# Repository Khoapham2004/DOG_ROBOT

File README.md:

# DOG_ROBOT
First, this project focuses on the research and development of a quadruped robot (Dog Robot). Our team used the mechanical design of the open-source DINGO Quadruped Robot as a reference. The electronic hardware, PCB design, overall kinematics, control algorithms, and software source code were entirely designed and implemented by our team.

This GitHub repository includes the complete project source code, including the Raspberry Pi software, image processing module, robot control commands, firmware for the custom PCB, the software developed to operate the robot, and the complete electrical schematic of the system.

GENERAL

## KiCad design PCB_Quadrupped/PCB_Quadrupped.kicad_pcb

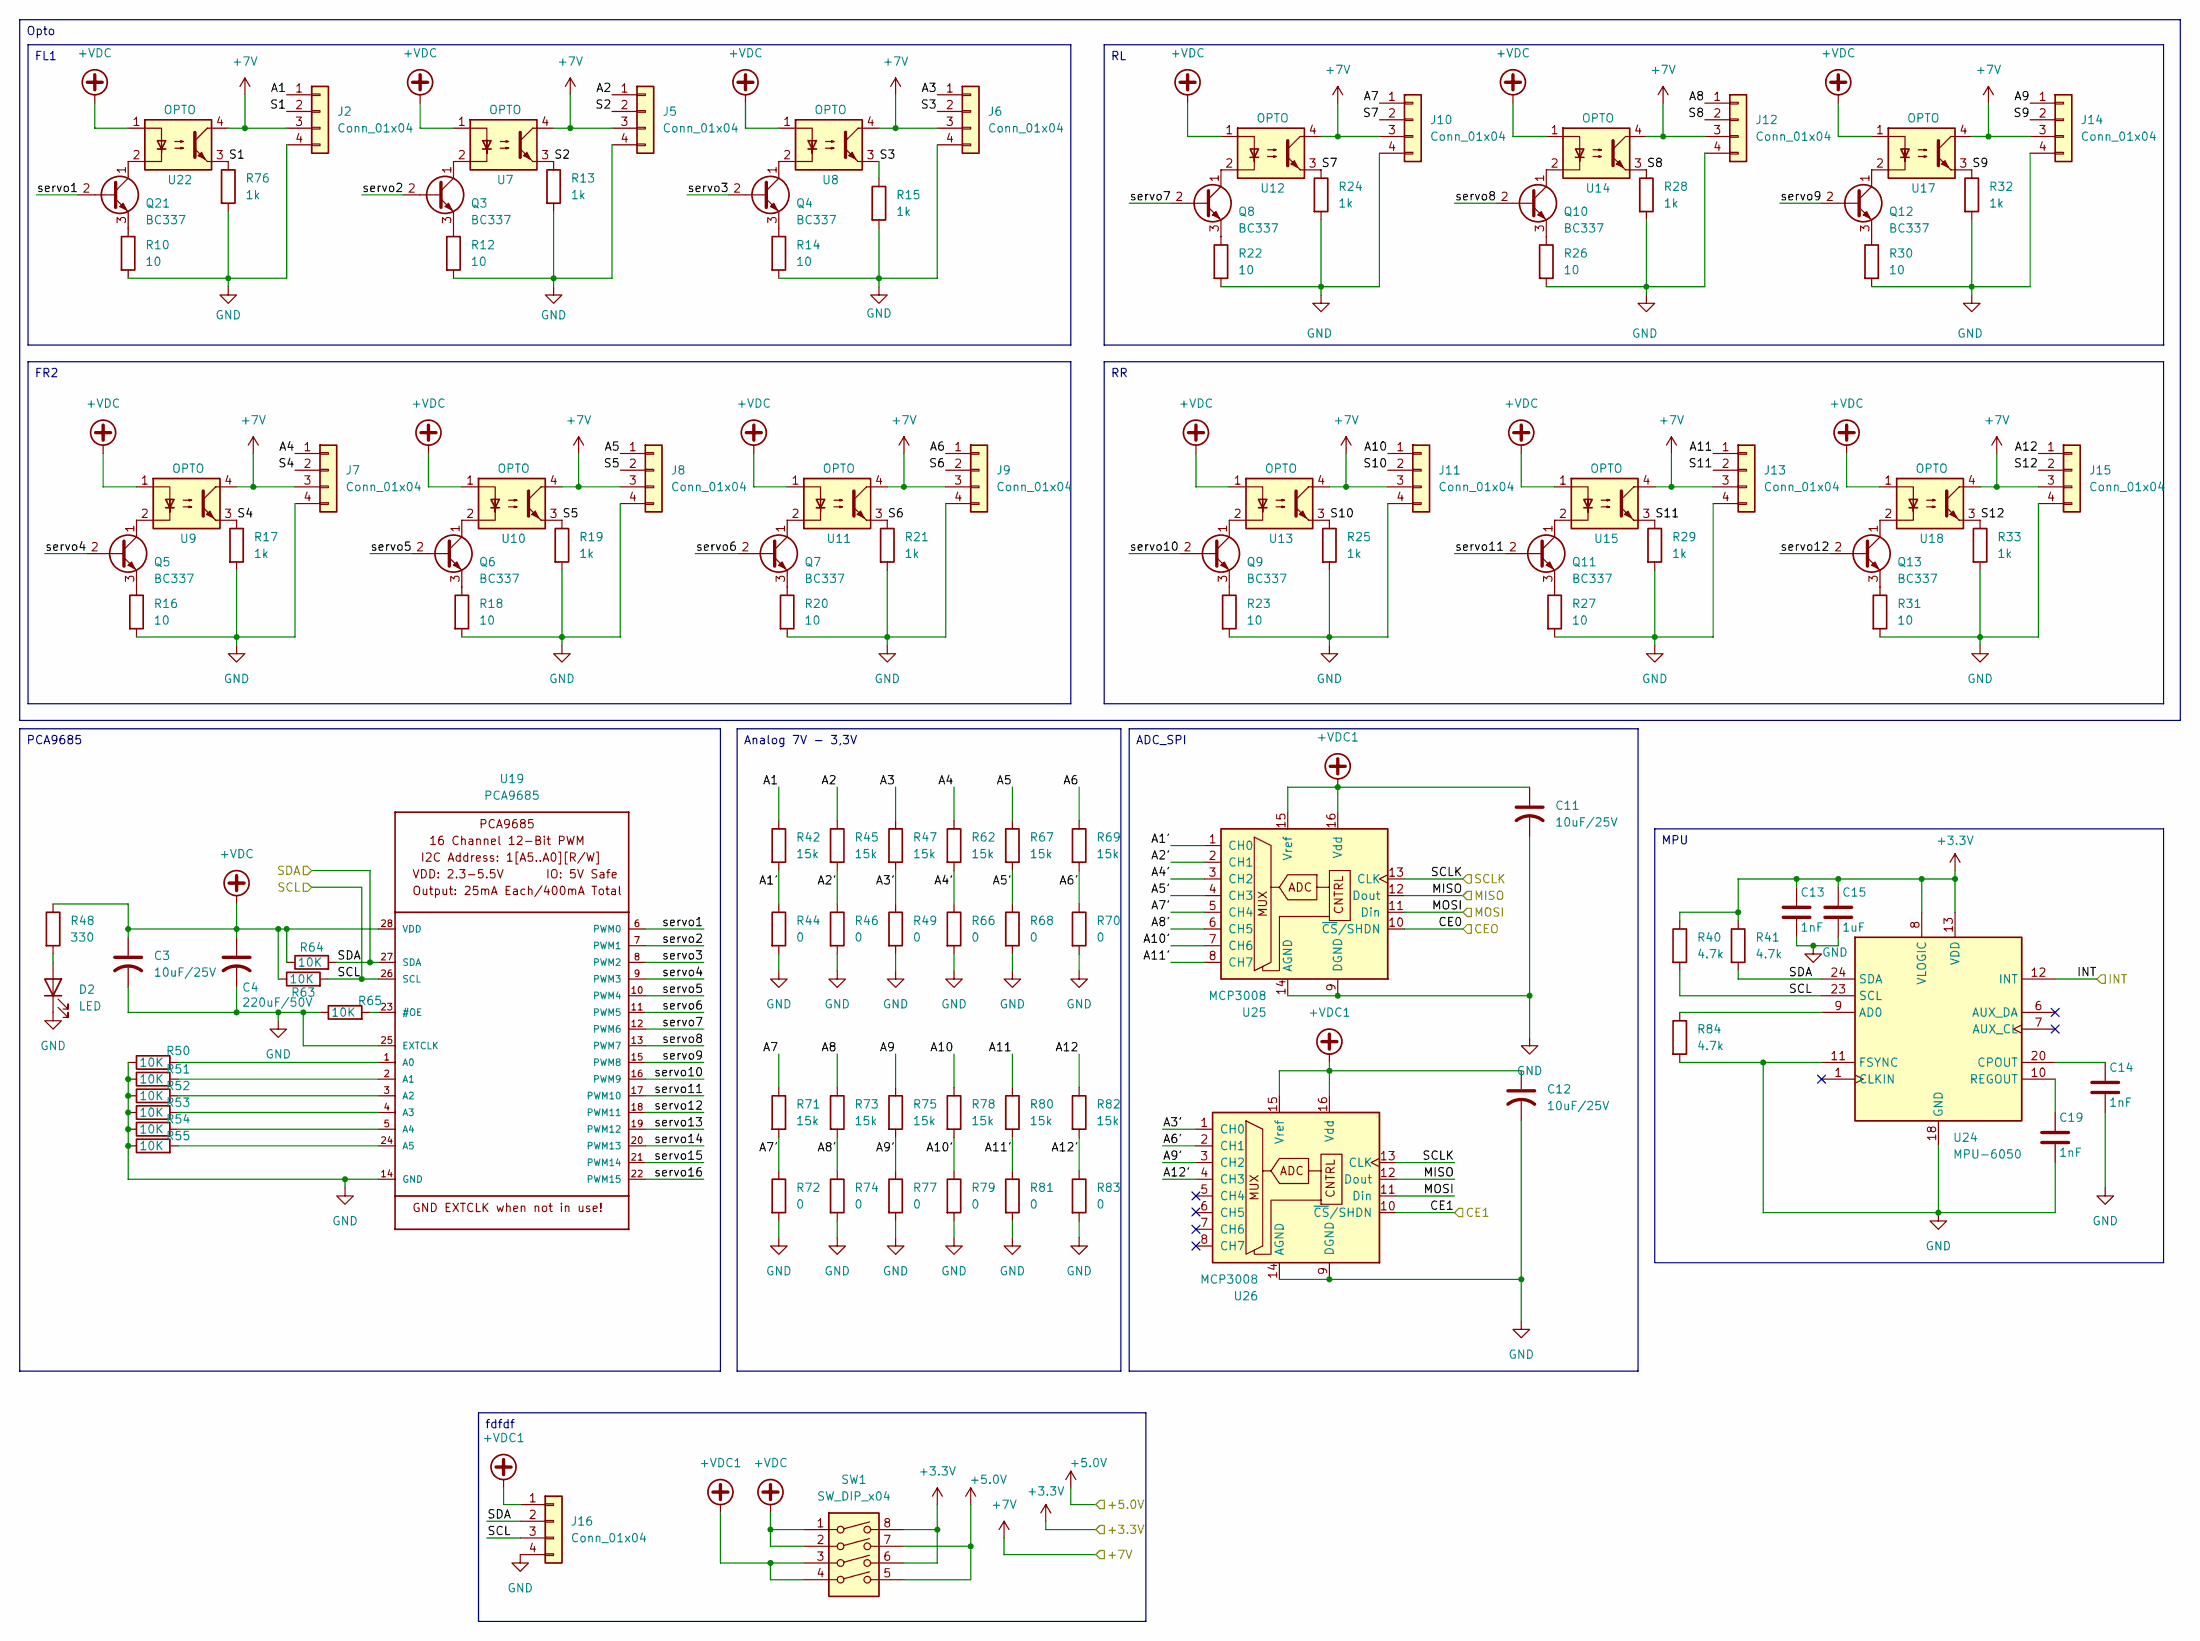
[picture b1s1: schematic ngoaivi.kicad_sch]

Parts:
C3, C11, C12: 10uF/25V; CP_Elec_4x4.5
C4: 220uF/50V; CP_Elec_10x10.5
C13, C14, C19: 1nF; C_0805_2012Metric
C15: 1uF; C_0805_2012Metric
D2: LED; LED_0805_2012Metric
J2, J5, J6, J7, J8, J9, J10, J11, J12, J13, J14, J15: Conn_01x04; JST_B4B-XH-A_LF__SN_
J16: Conn_01x04; PinHeader_1x04_P2.54mm_Vertical_SMD_Pin1Right
Q3, Q4, Q5, Q6, Q7, Q8, Q9, Q10, Q11, Q12, Q13, Q21: BC337; TO-92_Inline
R10, R12, R14, R16, R18, R20, R22, R23, R26, R27, R30, R31: 10; R_0805_2012Metric_Pad1.20x1.40mm_HandSolder
R13, R15, R17, R19, R21, R24, R25, R28, R29, R32, R33, R76: 1k; R_0805_2012Metric_Pad1.20x1.40mm_HandSolder
R40, R41, R84: 4.7k; R_0805_2012Metric_Pad1.20x1.40mm_HandSolder
R42, R45, R47, R62, R67, R69, R71, R73, R75, R78, R80, R82: 15k; R_0805_2012Metric_Pad1.20x1.40mm_HandSolder
R44, R46, R49, R66, R68, R70, R72, R74, R77, R79, R81, R83: 0; R_0805_2012Metric_Pad1.20x1.40mm_HandSolder
R48: 330; R_0805_2012Metric_Pad1.20x1.40mm_HandSolder
R50, R51, R52, R53, R54, R55, R63, R64, R65: 10K; R_0805_2012Metric_Pad1.20x1.40mm_HandSolder
SW1: SW_DIP_x04; SW_DIP_SPSTx04_Slide_9.78x12.34mm_W7.62mm_P2.54mm
U7, U8, U9, U10, U11, U12, U13, U14, U15, U17, U18, U22: OPTO; OptoIsolation-EL357N-G
U19: PCA9685; TSSOP28
U24: MPU-6050; InvenSense_QFN-24_4x4mm_P0.5mm
U25, U26: MCP3008; DIP16-2.54-19.2X7.62MM

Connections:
+3.3V: C13.1, C15.1, R40.1, R41.1, SW1.6, SW1.8, U24.8 (VLOGIC), U24.13 (VDD); also elsewhere on the board
+5.0V: SW1.5, SW1.7; also elsewhere on the board
+7V: J2.3, J5.3, J6.3, J7.3, J8.3, J9.3, J10.3, J11.3, J12.3, J13.3, J14.3, J15.3, U7.4, U8.4, U9.4, U10.4, U11.4, U12.4, U13.4, U14.4, U15.4, U17.4, U18.4, U22.4; also elsewhere on the board
+VDC: C3.1, C4.1, R48.1, R63.1, R64.1, SW1.1, SW1.2, U7.1, U8.1, U9.1, U10.1, U11.1, U12.1, U13.1, U14.1, U15.1, U17.1, U18.1, U19.28 (VDD), U22.1
+VDC1: C11.1, C12.1, J16.1, SW1.3, SW1.4, U25.15 (Vref), U25.16 (Vdd), U26.15 (Vref), U26.16 (Vdd)
/Ngoại vi/A1: J2.1, R42.1
/Ngoại vi/A1': R42.2, R44.1, U25.1 (CH0)
/Ngoại vi/A2: J5.1, R45.1
/Ngoại vi/A2': R45.2, R46.1, U25.2 (CH1)
/Ngoại vi/A3: J6.1, R47.1
/Ngoại vi/A3': R47.2, R49.1, U26.1 (CH0)
/Ngoại vi/A4: J7.1, R62.1
/Ngoại vi/A4': R62.2, R66.1, U25.3 (CH2)
/Ngoại vi/A5: J8.1, R67.1
/Ngoại vi/A5': R67.2, R68.1, U25.4 (CH3)
/Ngoại vi/A6: J9.1, R69.1
/Ngoại vi/A6': R69.2, R70.1, U26.2 (CH1)
/Ngoại vi/A7: J10.1, R71.1
/Ngoại vi/A7': R71.2, R72.1, U25.5 (CH4)
/Ngoại vi/A8: J12.1, R73.1
/Ngoại vi/A8': R73.2, R74.1, U25.6 (CH5)
/Ngoại vi/A9: J14.1, R75.1
/Ngoại vi/A9': R75.2, R77.1, U26.3 (CH2)
/Ngoại vi/A10: J11.1, R78.1
/Ngoại vi/A10': R78.2, R79.1, U25.7 (CH6)
/Ngoại vi/A11: J13.1, R80.1
/Ngoại vi/A11': R80.2, R81.1, U25.8 (CH7)
/Ngoại vi/A12: J15.1, R82.1
/Ngoại vi/A12': R82.2, R83.1, U26.4 (CH3)
/Ngoại vi/CE0: U25.10 (~CS/SHDN); also elsewhere on the board
/Ngoại vi/CE1: U26.10 (~CS/SHDN); also elsewhere on the board
/Ngoại vi/INT: U24.12 (INT); also elsewhere on the board
/Ngoại vi/MISO: U25.12 (Dout), U26.12 (Dout); also elsewhere on the board
/Ngoại vi/MOSI: U25.11 (Din), U26.11 (Din); also elsewhere on the board
/Ngoại vi/S1: J2.2, R76.1, U22.3
/Ngoại vi/S2: J5.2, R13.1, U7.3
/Ngoại vi/S3: J6.2, R15.1, U8.3
/Ngoại vi/S4: J7.2, R17.1, U9.3
/Ngoại vi/S5: J8.2, R19.1, U10.3
/Ngoại vi/S6: J9.2, R21.1, U11.3
/Ngoại vi/S7: J10.2, R24.1, U12.3
/Ngoại vi/S8: J12.2, R28.1, U14.3
/Ngoại vi/S9: J14.2, R32.1, U17.3
/Ngoại vi/S10: J11.2, R25.1, U13.3
/Ngoại vi/S11: J13.2, R29.1, U15.3
/Ngoại vi/S12: J15.2, R33.1, U18.3
/Ngoại vi/SCL: J16.3, R40.2, R63.2, U19.26 (SCL), U24.23 (SCL); also elsewhere on the board
/Ngoại vi/SCLK: U25.13 (CLK), U26.13 (CLK); also elsewhere on the board
/Ngoại vi/SDA: J16.2, R41.2, R64.2, U19.27 (SDA), U24.24 (SDA); also elsewhere on the board
/Ngoại vi/servo1: Q21.2 (B), U19.6 (PWM0)
/Ngoại vi/servo2: Q3.2 (B), U19.7 (PWM1)
/Ngoại vi/servo3: Q4.2 (B), U19.8 (PWM2)
/Ngoại vi/servo4: Q5.2 (B), U19.9 (PWM3)
/Ngoại vi/servo5: Q6.2 (B), U19.10 (PWM4)
/Ngoại vi/servo6: Q7.2 (B), U19.11 (PWM5)
/Ngoại vi/servo7: Q8.2 (B), U19.12 (PWM6)
/Ngoại vi/servo8: Q10.2 (B), U19.13 (PWM7)
/Ngoại vi/servo9: Q12.2 (B), U19.15 (PWM8)
/Ngoại vi/servo10: Q9.2 (B), U19.16 (PWM9)
/Ngoại vi/servo11: Q11.2 (B), U19.17 (PWM10)
/Ngoại vi/servo12: Q13.2 (B), U19.18 (PWM11)
/Ngoại vi/servo13: U19.19 (PWM12)
/Ngoại vi/servo14: U19.20 (PWM13)
/Ngoại vi/servo15: U19.21 (PWM14)
/Ngoại vi/servo16: U19.22 (PWM15)
GND: C3.2, C4.2, C11.2, C12.2, C13.2, C14.2, C15.2, C19.2, D2.1 (K), J2.4, J5.4, J6.4, J7.4, J8.4, J9.4, J10.4, J11.4, J12.4, J13.4, J14.4, J15.4, J16.4, R10.2, R12.2, R13.2, R14.2, R15.2, R16.2, R17.2, R18.2, R19.2, R20.2, R21.2, R22.2, R23.2, R24.2, R25.2, R26.2, R27.2, R28.2, R29.2, R30.2, R31.2, R32.2, R33.2, R44.2, R46.2, R49.2, R50.1, R51.1, R52.1, R53.1, R54.1, R55.1, R65.1, R66.2, R68.2, R70.2, R72.2, R74.2, R76.2, R77.2, R79.2, R81.2, R83.2, R84.2, U19.14 (GND), U19.25 (EXTCLK), U24.11 (FSYNC), U24.18 (GND), U25.9 (DGND), U25.14 (AGND), U26.9 (DGND), U26.14 (AGND); also elsewhere on the board
unnamed: D2.2 (A), R48.2
unnamed: Q3.1 (C), U7.2
unnamed: Q3.3 (E), R12.1
unnamed: Q4.1 (C), U8.2
unnamed: Q4.3 (E), R14.1
unnamed: Q5.1 (C), U9.2
unnamed: Q5.3 (E), R16.1
unnamed: Q6.1 (C), U10.2
unnamed: Q6.3 (E), R18.1
unnamed: Q7.1 (C), U11.2
unnamed: Q7.3 (E), R20.1
unnamed: Q8.1 (C), U12.2
unnamed: Q8.3 (E), R22.1
unnamed: Q9.1 (C), U13.2
unnamed: Q9.3 (E), R23.1
unnamed: Q10.1 (C), U14.2
unnamed: Q10.3 (E), R26.1
unnamed: Q11.1 (C), U15.2
unnamed: Q11.3 (E), R27.1
unnamed: Q12.1 (C), U17.2
unnamed: Q12.3 (E), R30.1
unnamed: Q13.1 (C), U18.2
unnamed: Q13.3 (E), R31.1
unnamed: Q21.1 (C), U22.2
unnamed: Q21.3 (E), R10.1
unnamed: R65.2, U19.23 (#OE)
unnamed: R50.2, U19.1 (A0)
unnamed: R51.2, U19.2 (A1)
unnamed: R52.2, U19.3 (A2)
unnamed: R53.2, U19.4 (A3)
unnamed: R54.2, U19.5 (A4)
unnamed: R55.2, U19.24 (A5)
unnamed: R84.1, U24.9 (AD0)
unnamed: C14.1, U24.20 (CPOUT)
unnamed: C19.1, U24.10 (REGOUT)

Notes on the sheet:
ADC_SPI
PCA9685
Opto
fdfdf
FR2
MPU
Analog 7V - 3,3V
FL1

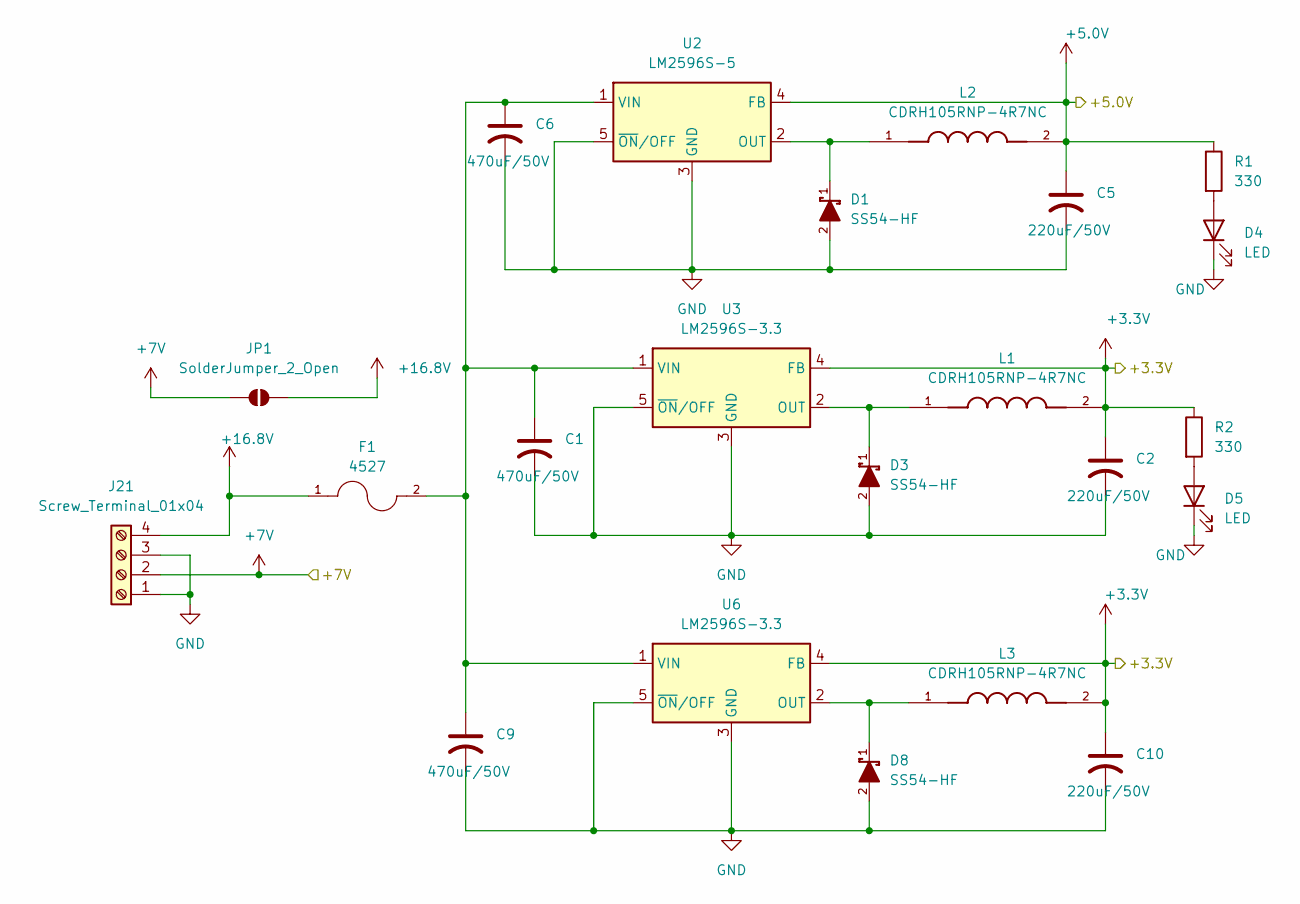
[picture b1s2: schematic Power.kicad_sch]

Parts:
C1, C6, C9: 470uF/50V; CP_Elec_10x10.5
C2, C5, C10: 220uF/50V; CP_Elec_10x10.5
D1, D3, D8: SS54-HF; DIOM5025X220N; MOUSER_PART_NUMBER 750-SS54-HF
D4, D5: LED; LED_0805_2012Metric
F1: 4527; FUSE_4527
J21: Screw_Terminal_01x04; PhoenixContact_MSTBA_2,5_4-G-5,08_1x04_P5.08mm_Horizontal
JP1: SolderJumper_2_Open; SolderJumper-2_P1.3mm_Open_RoundedPad1.0x1.5mm
L1, L2, L3: CDRH105RNP-4R7NC; IND_CDRH105RNP-4R7NC; PARTREV 23-Oct-2017
R1, R2: 330; R_0805_2012Metric_Pad1.20x1.40mm_HandSolder
U2: LM2596S-5; TO-263-5_TabPin3
U3, U6: LM2596S-3.3; TO-263-5_TabPin3

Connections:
+3.3V: C2.1, C10.1, L1.2, L3.2, R2.1, U3.4 (FB), U6.4 (FB); also elsewhere on the board
+5.0V: C5.1, L2.2, R1.1, U2.4 (FB); also elsewhere on the board
+7V: J21.2, JP1.1 (A); also elsewhere on the board
+16.8V: F1.1, J21.4, JP1.2 (B)
GND: C1.2, C2.2, C5.2, C6.2, C9.2, C10.2, D1.2, D3.2, D4.1 (K), D5.1 (K), D8.2, J21.1, J21.3, U2.3 (GND), U2.5 (~ON/OFF), U3.3 (GND), U3.5 (~ON/OFF), U6.3 (GND), U6.5 (~ON/OFF); also elsewhere on the board
unnamed: D4.2 (A), R1.2
unnamed: D5.2 (A), R2.2
unnamed: D1.1, L2.1, U2.2 (OUT)
unnamed: C1.1, C6.1, C9.1, F1.2, U2.1 (VIN), U3.1 (VIN), U6.1 (VIN)
unnamed: D3.1, L1.1, U3.2 (OUT)
unnamed: D8.1, L3.1, U6.2 (OUT)

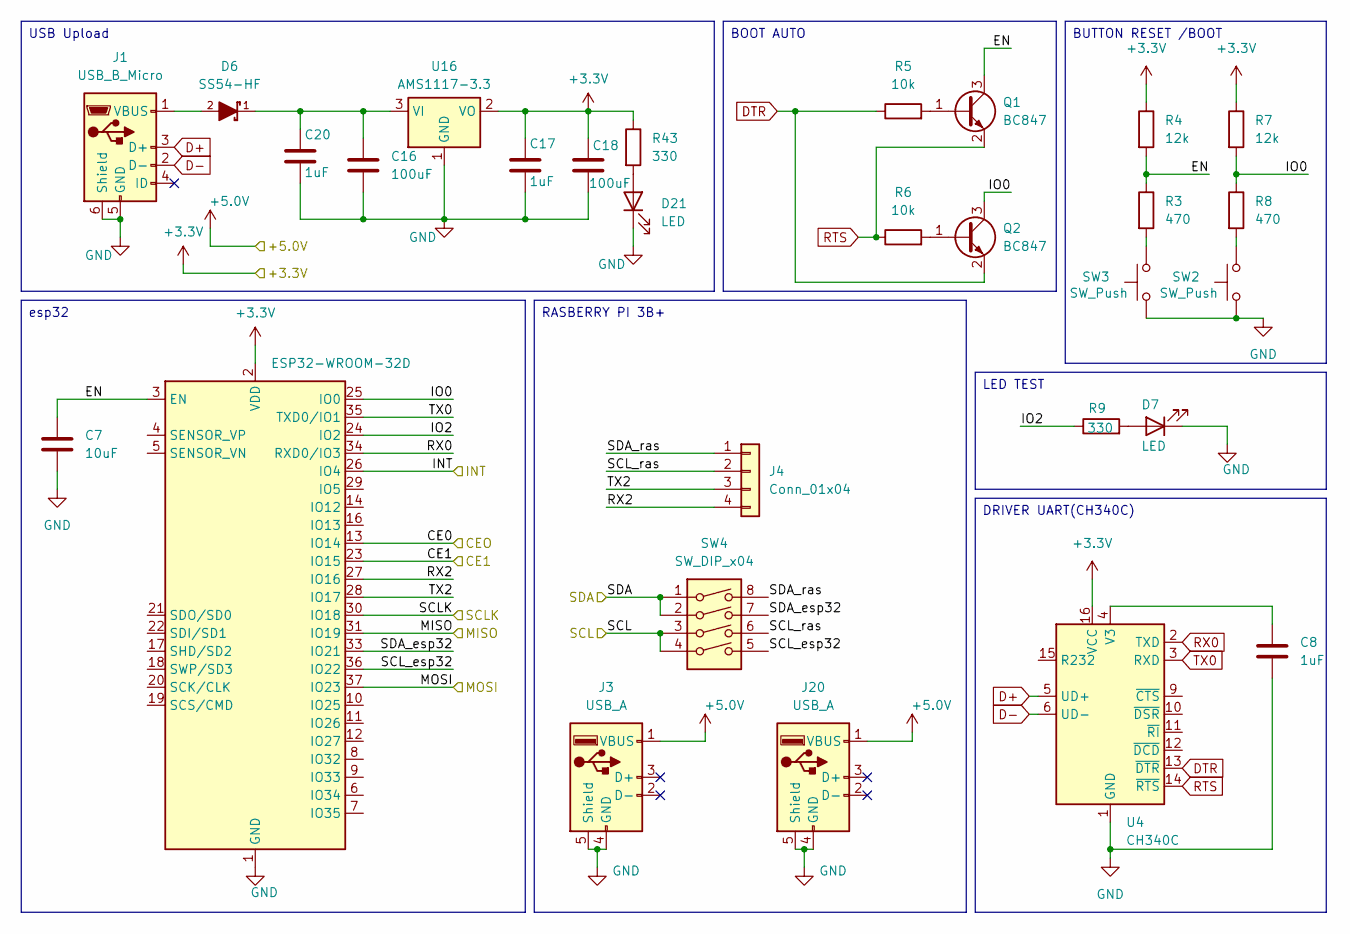
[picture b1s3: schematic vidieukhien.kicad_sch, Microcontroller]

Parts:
C7: 10uF; C_0805_2012Metric_Pad1.18x1.45mm_HandSolder
C8, C17, C20: 1uF; C_0805_2012Metric_Pad1.18x1.45mm_HandSolder
C16, C18: 100uF; CP_Elec_6.3x5.4
D6: SS54-HF; DIOM5025X220N; MOUSER_PART_NUMBER 750-SS54-HF
D7, D21: LED; LED_0805_2012Metric
J1: USB_B_Micro; USB_Micro-B_Molex-105017-0001
J3: USB_A; USB_A_Stewart_SS-52100-001_Horizontal
J4: Conn_01x04; JST_B4B-XH-A_LF__SN_
J20: USB_A; USB_A_Kycon_KUSBX-AS1N-B_Horizontal
Q1, Q2: BC847; SOT-23
R3, R8: 470; R_0805_2012Metric_Pad1.20x1.40mm_HandSolder
R4, R7: 12k; R_0805_2012Metric_Pad1.20x1.40mm_HandSolder
R5, R6: 10k; R_0805_2012Metric_Pad1.20x1.40mm_HandSolder
R9, R43: 330; R_0805_2012Metric_Pad1.20x1.40mm_HandSolder
SW2, SW3: SW_Push; SW_Push_1P1T_NO_E-Switch_TL3301NxxxxxG
SW4: SW_DIP_x04; SW_DIP_SPSTx04_Slide_9.78x12.34mm_W7.62mm_P2.54mm
U1: ESP32-WROOM-32D
U4: CH340C; SOIC-16_3.9x9.9mm_P1.27mm
U16: AMS1117-3.3; SOT-223-3_TabPin2

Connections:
+3.3V: C17.1, C18.1, R4.1, R7.1, R43.1, U1.2 (VDD), U4.16 (VCC), U16.2 (VO); also elsewhere on the board
+5.0V: J3.1 (VBUS), J20.1 (VBUS); also elsewhere on the board
/Ngoại vi/CE0: U1.13 (IO14); also elsewhere on the board
/Ngoại vi/CE1: U1.23 (IO15); also elsewhere on the board
/Ngoại vi/INT: U1.26 (IO4); also elsewhere on the board
/Ngoại vi/MISO: U1.31 (IO19); also elsewhere on the board
/Ngoại vi/MOSI: U1.37 (IO23); also elsewhere on the board
/Ngoại vi/SCL: SW4.3, SW4.4; also elsewhere on the board
/Ngoại vi/SCLK: U1.30 (IO18); also elsewhere on the board
/Ngoại vi/SDA: SW4.1, SW4.2; also elsewhere on the board
/microcontroler/EN: C7.1, Q1.3 (C), R3.1, R4.2, U1.3 (EN)
/microcontroler/IO0: Q2.3 (C), R7.2, R8.1, U1.25 (IO0)
/microcontroler/IO2: R9.1, U1.24 (IO2)
/microcontroler/RX2: J4.4, U1.27 (IO16)
/microcontroler/SCL_esp32: SW4.5, U1.36 (IO22)
/microcontroler/SCL_ras: J4.2, SW4.6
/microcontroler/SDA_esp32: SW4.7, U1.33 (IO21)
/microcontroler/SDA_ras: J4.1, SW4.8
/microcontroler/TX2: J4.3, U1.28 (IO17)
D+: J1.3 (D+), U4.5 (UD+)
D-: J1.2 (D-), U4.6 (UD-)
DTR: Q2.2 (E), R5.1, U4.13 (~DTR)
GND: C7.2, C8.2, C16.2, C17.2, C18.2, C20.2, D7.1 (K), D21.1 (K), J1.5 (GND), J1.6 (Shield), J3.4 (GND), J3.5 (Shield), J20.4 (GND), J20.5 (Shield), SW2.1, SW3.1, U1.1 (GND), U1.15 (GND), U1.38 (GND), U1.39 (GND), U4.1 (GND), U16.1 (GND); also elsewhere on the board
unnamed: D7.2 (A), R9.2
unnamed: D21.2 (A), R43.2
unnamed: D6.2, J1.1 (VBUS)
unnamed: Q1.1 (B), R5.2
unnamed: Q2.1 (B), R6.2
unnamed: R3.2, SW3.2
unnamed: R8.2, SW2.2
unnamed: C8.1, U4.4 (V3)
unnamed: C16.1, C20.1, D6.1, U16.3 (VI)
RTS: Q1.2 (E), R6.1, U4.14 (~RTS)
RX0: U1.34 (RXD0/IO3), U4.2 (TXD)
TX0: U1.35 (TXD0/IO1), U4.3 (RXD)

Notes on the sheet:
BUTTON RESET /BOOT
DRIVER UART(CH340C)
esp32
RASBERRY PI 3B+
LED TEST
USB Upload
BOOT AUTO

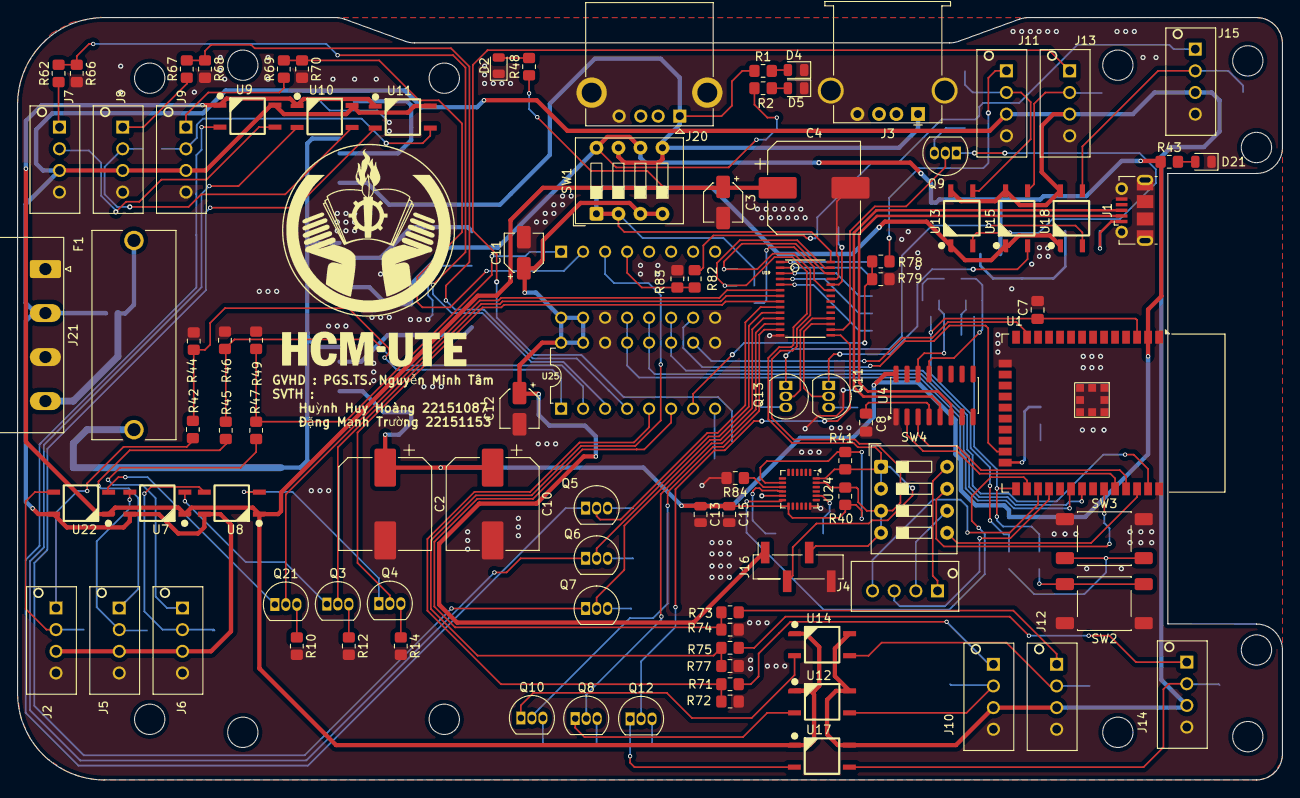
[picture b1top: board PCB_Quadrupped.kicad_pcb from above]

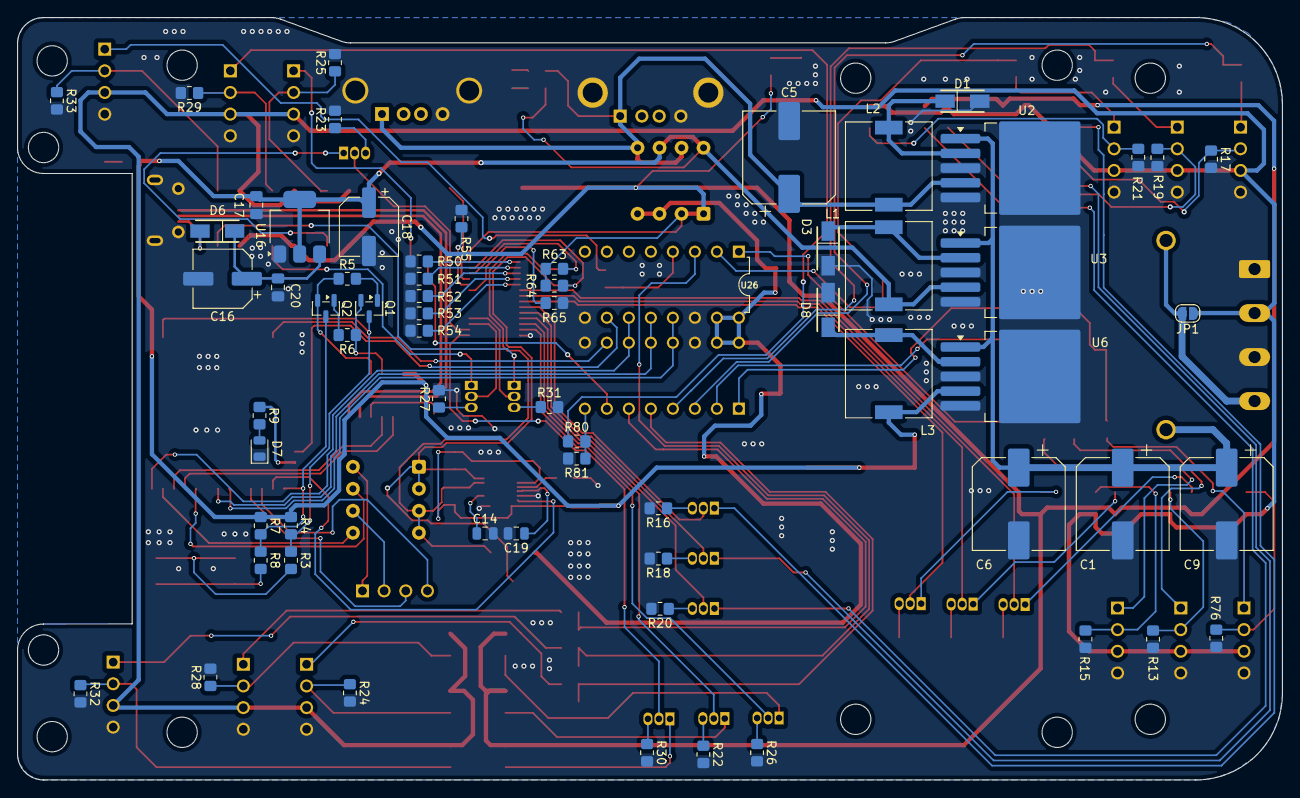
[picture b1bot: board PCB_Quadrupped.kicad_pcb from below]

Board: 2 copper layers, 146.0 x 88.0 mm, 163 parts (65 on the bottom side), 128 nets.

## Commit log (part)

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2026-02-11 Update README with project details and instructions
    Added project description and usage instructions.
